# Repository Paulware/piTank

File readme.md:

<h1>Pi Tank</h1>
  This project will allow you to drive a vehicle using a laptop, optionally, you can watch 
  a a video stream on the laptop from a raspberry pi camera, mounted on the vehicle. <br>
  
<h2>Components</h2>
   <ul>
      <li>Raspberry Pi4</li>
      <li>Raspberry pi camera</li>
      <li>Raspberry motor driver pi-hat (available from <a href="https://www.adeept.com/adeept-motor-hat-for-raspberry-pi-smart-robot-car-driver_p0133.html">adeept</a>)</li>
   </ul>
   
   A lot of the testing and setup can be done without a vehicle.
   
<h1><a href="http://Paulware.github.io/piTank/docs/index.html">Step By Step Instructions (organized as test steps)</a></h1>
<hr>
<b>Note</b>  Adeept also has a similar (but different) project described: <a href="https://www.adeept.com/learn/detail-33.html">here</a>

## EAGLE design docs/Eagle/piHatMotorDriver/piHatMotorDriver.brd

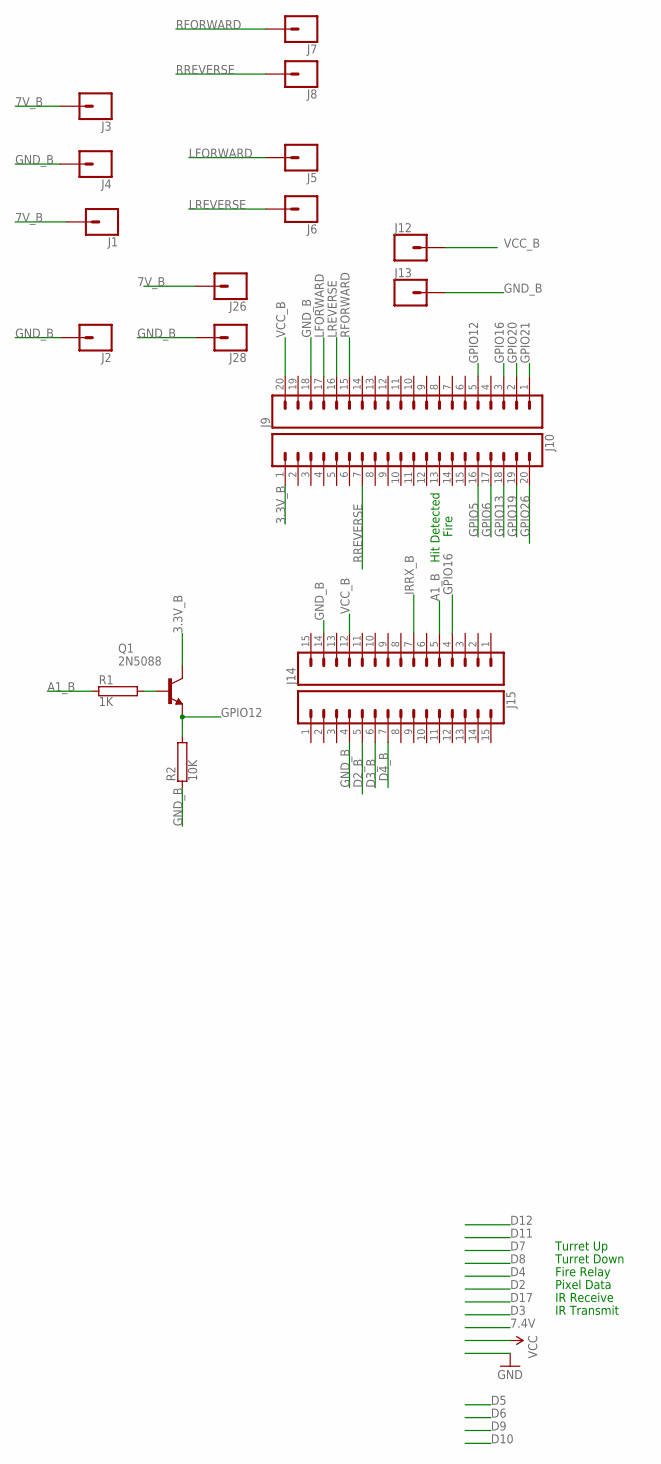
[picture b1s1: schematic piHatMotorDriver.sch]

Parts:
J1, J2, J3, J4, J5, J6, J7, J8, J12, J13, J26, J28: CONN_01; 1X01
J9, J10: CONN_20; 1X20
J14, J15: CONN_15; 1X15
Q1: 2N5088; TO92
R1: 1K; CA0001
R2: 10K; CA0001

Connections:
3.3V_B: J10.1, Q1.1 (C)
7V_B: J1.1, J3.1, J26.1; also elsewhere on the board
A1_B: J14.5, R1.1
D2_B: J15.5
D3_B: J15.6
D4_B: J15.7
GND_B: J2.1, J4.1, J9.18, J13.1, J14.14, J15.4, J28.1, R2.1; also elsewhere on the board
GPIO5: J10.16
GPIO6: J10.17
GPIO12: J9.5, Q1.3 (E), R2.2
GPIO13: J10.18
GPIO16: J9.3, J14.4
GPIO19: J10.19
GPIO20: J9.2; also elsewhere on the board
GPIO21: J9.1; also elsewhere on the board
GPIO26: J10.20
IRRX_B: J14.7
LFORWARD: J5.1, J9.17
LREVERSE: J6.1, J9.16
unnamed: Q1.2 (B), R1.2
RFORWARD: J7.1, J9.15
RREVERSE: J8.1, J10.7
VCC_B: J9.20, J12.1, J14.12

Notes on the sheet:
Turret Up
Turret Down
Fire Relay
Pixel Data
IR Receive
IR Transmit
Hit Detected
Fire

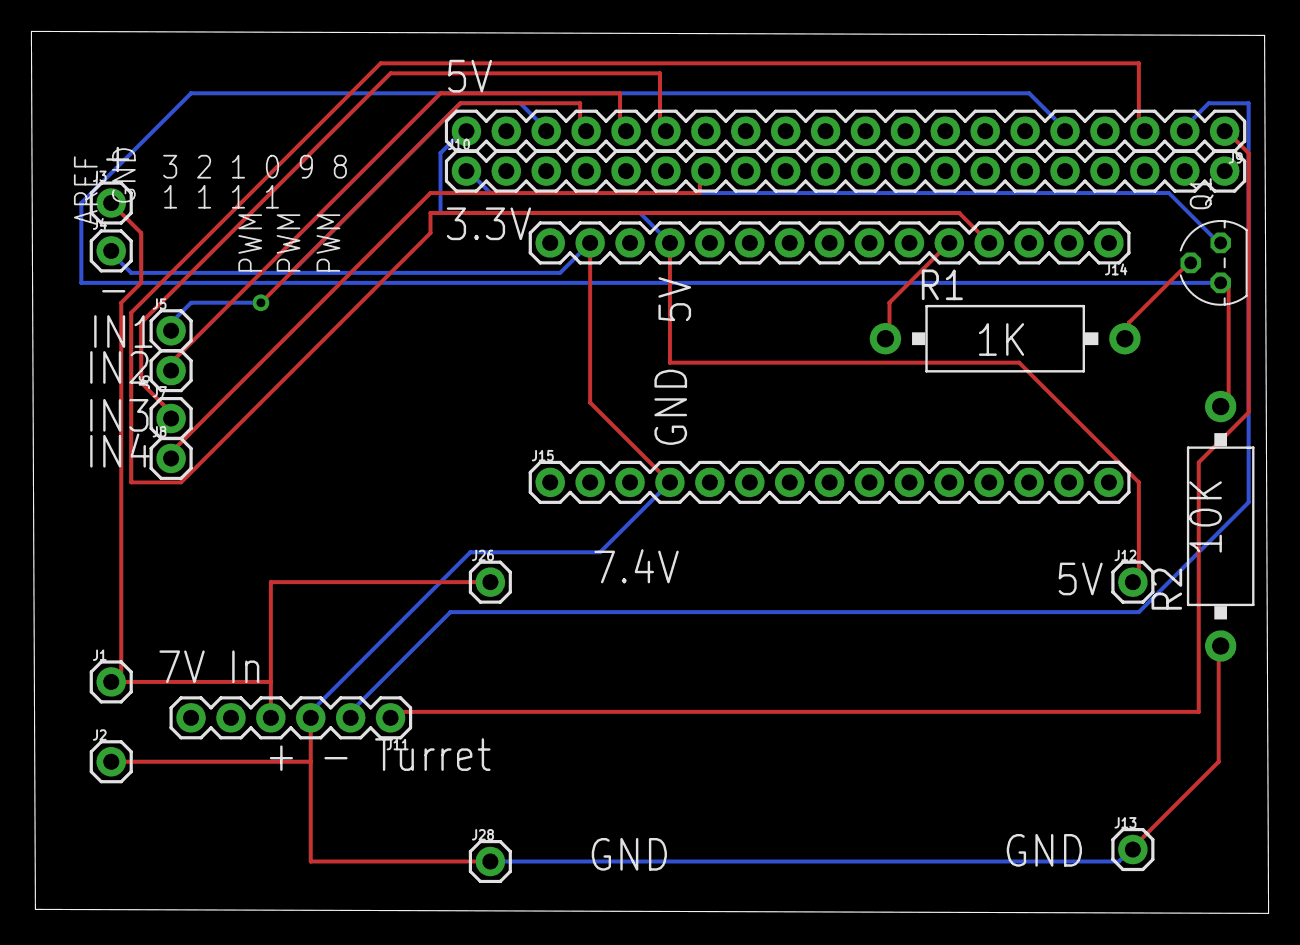
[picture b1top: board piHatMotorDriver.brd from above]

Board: 2 copper layers, 78.7 x 56.1 mm, 20 parts (0 on the bottom side), 14 nets.

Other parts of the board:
J11: 1X06

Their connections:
7V_B: J11.4; also elsewhere on the board
GND_B: J11.3; also elsewhere on the board
GPIO20: J11.2; also elsewhere on the board
GPIO21: J11.1; also elsewhere on the board

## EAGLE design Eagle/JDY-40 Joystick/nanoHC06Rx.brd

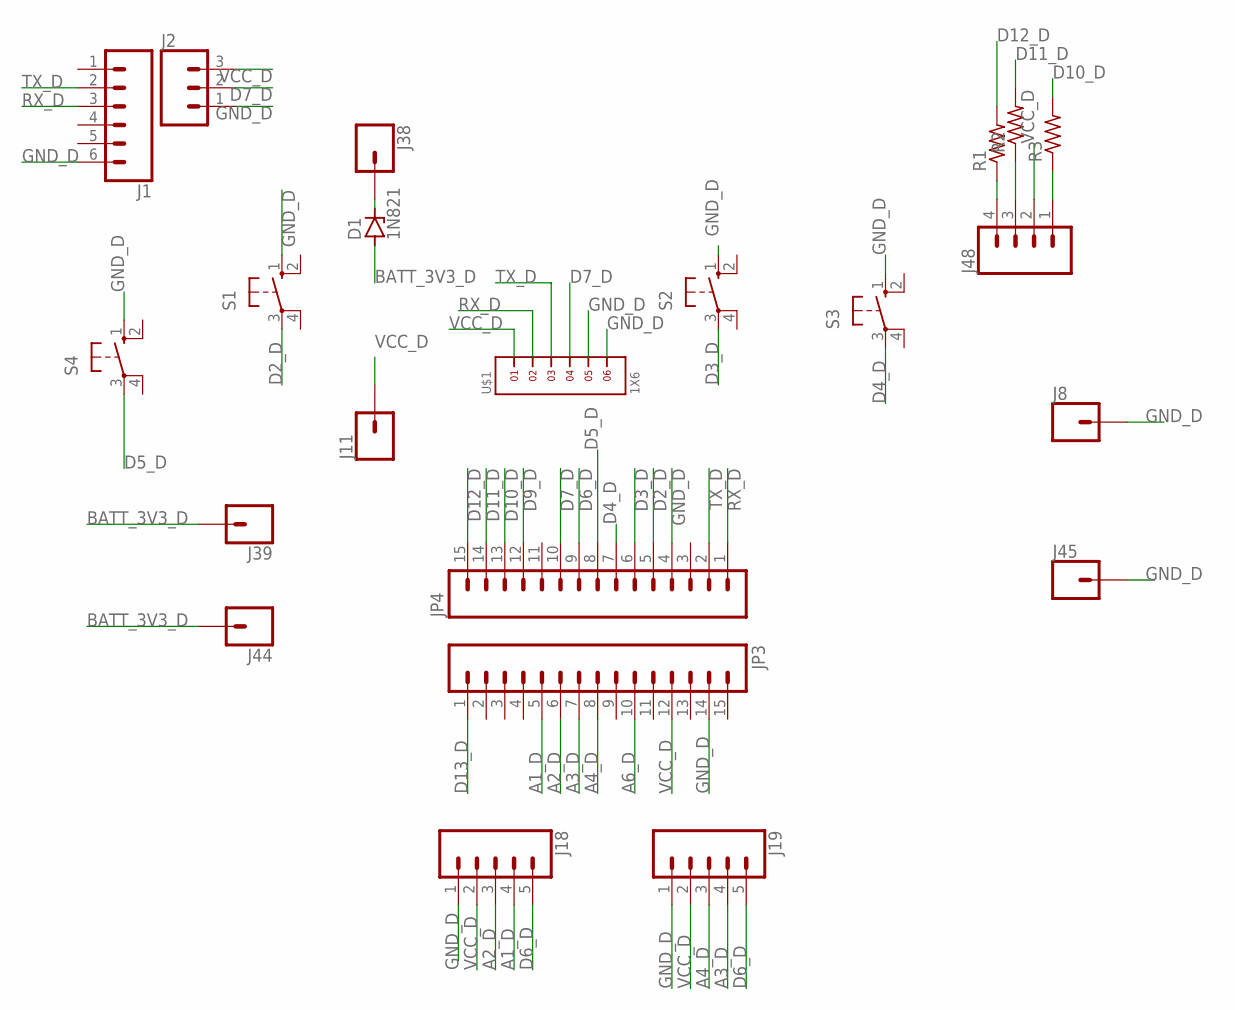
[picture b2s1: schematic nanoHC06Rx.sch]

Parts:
D1: 1N821; DO35Z10
J1: CONN_06SILK_FEMALE_PTH; 1X06
J2: CONN_03; 1X03
J8, J11, J38, J39: CONN_01; 1X01
J18, J19: CONN_05; 1X05
J44, J45: CONN_01PTH_2MM; 1X01_2MM
J48: CONN_04; 1X04
JP3, JP4: M15; 1X15@1
R1, R2, R3: R-US_0309/10; 0309/10
S1, S2, S3, S4: 40-XX; B3F-40XX
U$1: 1X6

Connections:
A1_D: J18.4, JP3.5
A2_D: J18.3, JP3.6
A3_D: J19.4, JP3.7
A4_D: J19.3, JP3.8
A6_D: JP3.10
BATT_3V3_D: D1.A, J39.1, J44.1
D2_D: JP4.5, S1.3
D3_D: JP4.6, S2.3
D4_D: JP4.7, S3.3
D5_D: JP4.8, S4.3
D6_D: J18.5, J19.5, JP4.9
D7_D: J2.2, JP4.10, U$1.4
D9_D: JP4.12
D10_D: JP4.13, R3.2
D11_D: JP4.14, R2.2
D12_D: JP4.15, R1.2
D13_D: JP3.1
GND_D: J1.6, J2.1, J8.1, J18.1, J19.1, J45.1, JP3.14, JP4.4, S1.1 (S), S2.1 (S), S3.1 (S), S4.1 (S), U$1.5, U$1.6
unnamed: D1.C, J38.1
unnamed: J48.4, R1.1
unnamed: J48.3, R2.1
unnamed: J48.1, R3.1
RX_D: J1.3, JP4.1, U$1.2
TX_D: J1.2, JP4.2, U$1.3
VCC_D: J2.3, J11.1, J18.2, J19.2, J48.2, JP3.12, U$1.1

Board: 2 copper layers, 22 parts (0 on the bottom side), 22 nets, no tracks yet.

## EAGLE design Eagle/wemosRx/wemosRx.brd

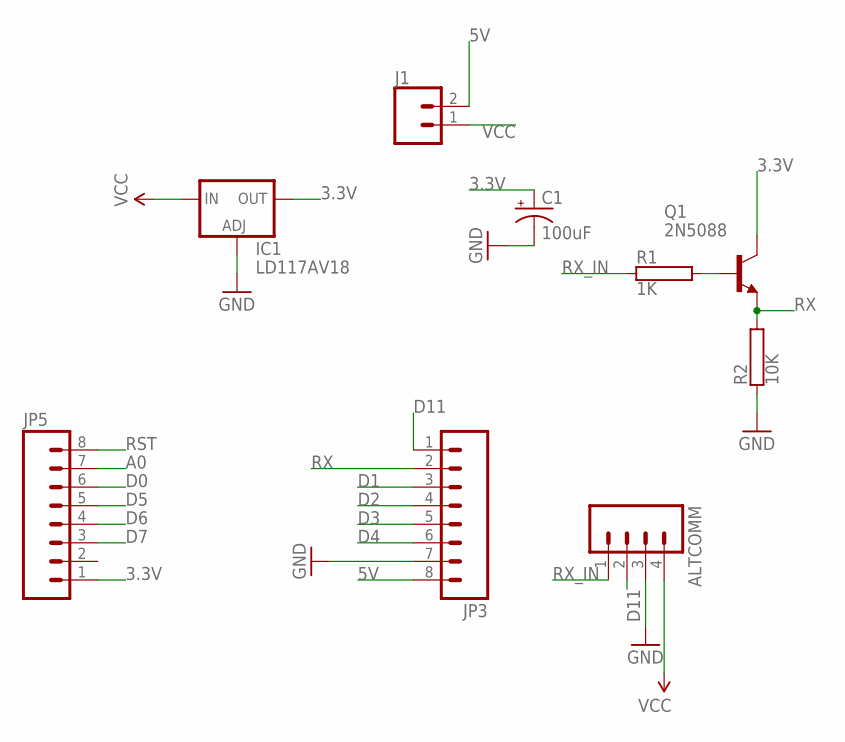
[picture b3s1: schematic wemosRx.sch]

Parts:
ALTCOMM: M04LONGPADS; 1X04_LONGPADS@1
C1: 100uF; CPOL-RADIAL-2.5MM-6.5MM
IC1: LD117AV18; TO220L1
J1: CONN_02; 1X02
JP3, JP5: M08LONGPADS; 1X08_LONGPADS
Q1: 2N5088; TO92
R1: 1K; RS1/4
R2: 10K; RS1/4

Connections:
3.3V: C1.1 (+), IC1.2 (OUT), JP5.1, Q1.1 (C)
5V: J1.2, JP3.8
A0: JP5.7
D0: JP5.6
D1: JP3.3
D2: JP3.4
D3: JP3.5
D4: JP3.6
D5: JP5.5
D6: JP5.4
D7: JP5.3
D11: ALTCOMM.2, JP3.1
GND: ALTCOMM.3, C1.2 (-), IC1.1 (ADJ), JP3.7, R2.1
unnamed: Q1.2 (B), R1.2
RST: JP5.8
RX: JP3.2, Q1.3 (E), R2.2
RX_IN: ALTCOMM.1, R1.1
VCC: ALTCOMM.4, IC1.3 (IN), J1.1

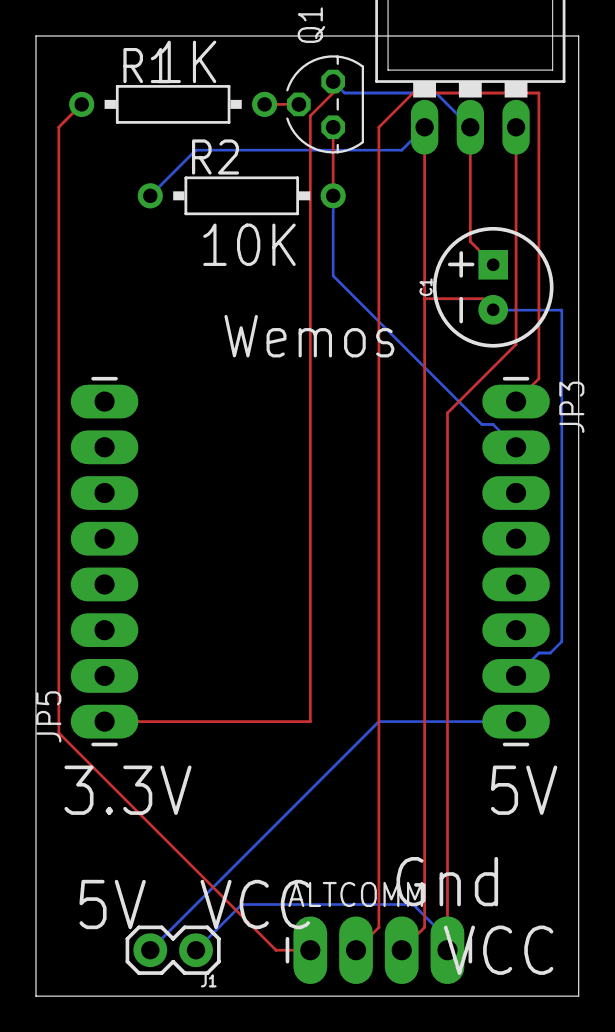
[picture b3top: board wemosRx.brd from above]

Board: 2 copper layers, 30.1 x 53.3 mm, 9 parts (0 on the bottom side), 8 nets.

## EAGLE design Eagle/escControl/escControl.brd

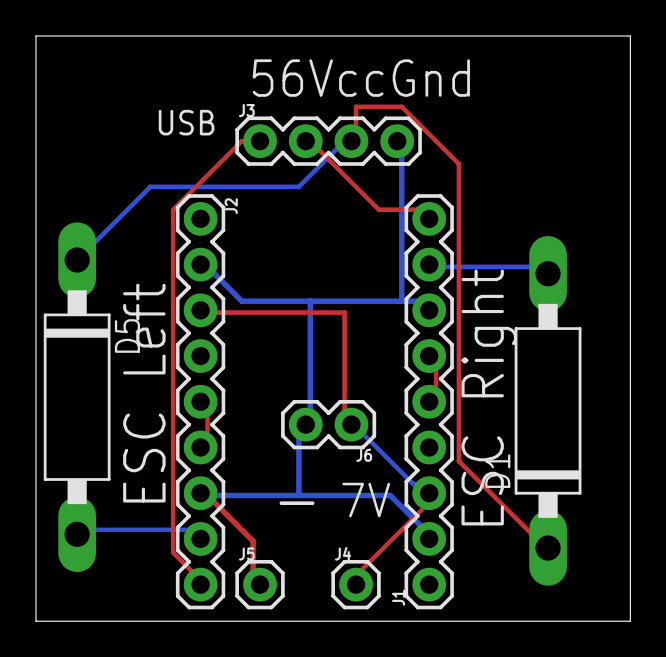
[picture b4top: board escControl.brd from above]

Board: 2 copper layers, 33.0 x 32.5 mm, 8 parts (0 on the bottom side), 9 nets.

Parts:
D1, D5: 1N5333; C1702-15
J1, J2: 1X09
J3: 1X04
J4, J5: 1X01
J6: 1X02

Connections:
7.4V: J1.3, J2.3, J4.1, J6.1
D5: J2.9, J3.1
D6: J1.9, J3.2
GND: J1.2, J1.7, J2.2, J2.7, J3.4, J5.1, J6.2
unnamed: D5.A, J2.8
unnamed: J2.5, J2.6
unnamed: D1.A, J1.8
unnamed: J1.5, J1.6
VCC: D1.C, D5.C, J3.3

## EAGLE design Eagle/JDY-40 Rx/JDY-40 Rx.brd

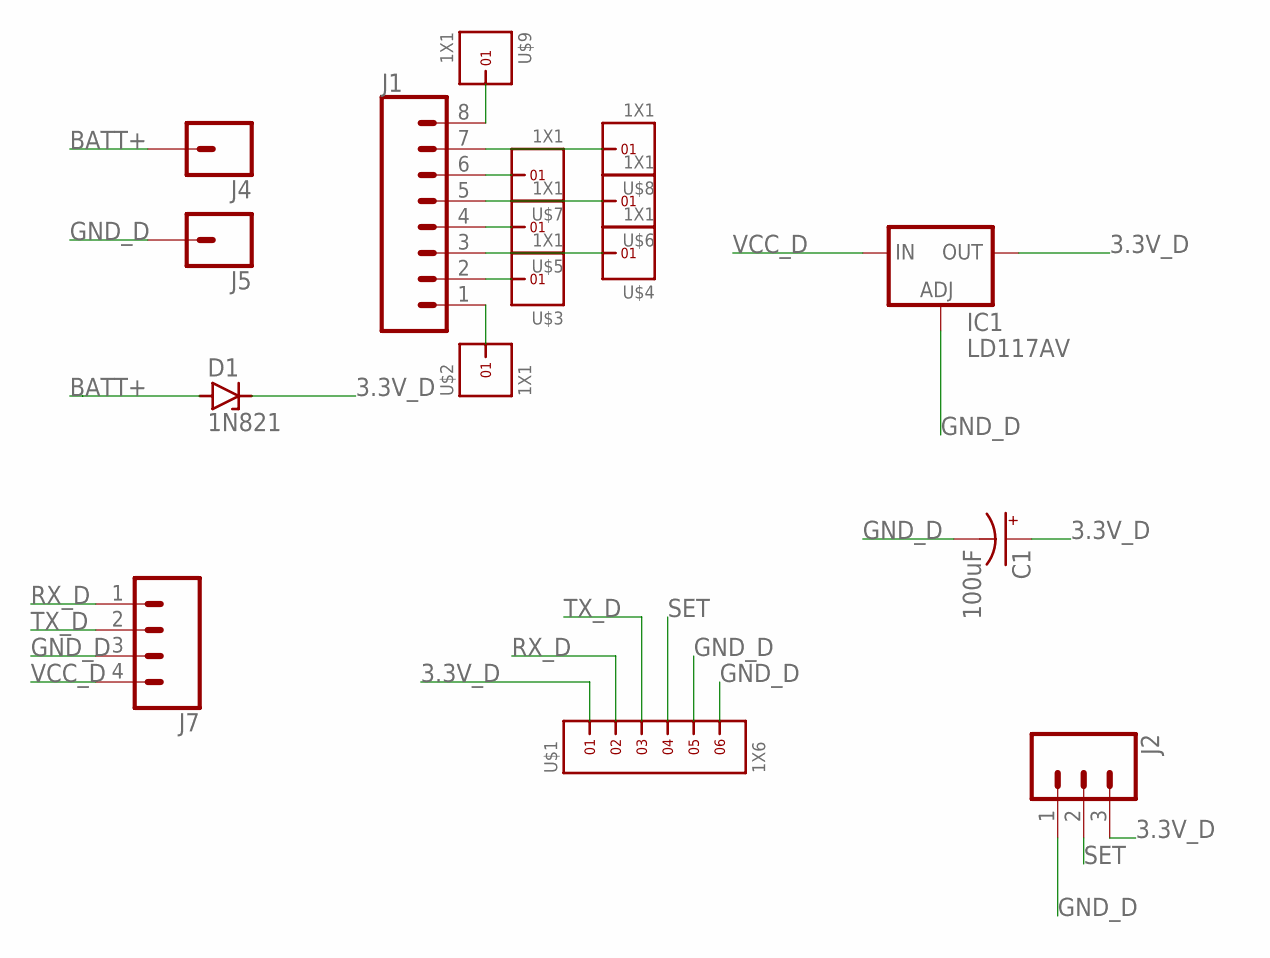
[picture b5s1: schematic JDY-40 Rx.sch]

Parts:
C1: 100uF; CPOL-RADIAL-2.5MM-6.5MM
D1: 1N821; DO35Z10
IC1: LD117AV; TO220L1
J1: CONN_08"; 1X08
J2: CONN_03; 1X03
J4, J5: CONN_01; 1X01
J7: CONN_04; 1X04
U$1: 1X6
U$2, U$3, U$4, U$5, U$6, U$7, U$8, U$9: 1X1

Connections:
3.3V_D: C1.1 (+), D1.C, IC1.2 (OUT), J2.3, U$1.1
BATT+: D1.A, J4.1
GND_D: C1.2 (-), IC1.1 (ADJ), J2.1, J5.1, J7.3, U$1.5, U$1.6
unnamed: J1.1, U$2.1
unnamed: J1.2, U$3.1
unnamed: J1.3, U$4.1
unnamed: J1.4, U$5.1
unnamed: J1.5, U$6.1
unnamed: J1.6, U$7.1
unnamed: J1.7, U$8.1
unnamed: J1.8, U$9.1
RX_D: J7.1, U$1.2
SET: J2.2, U$1.4
TX_D: J7.2, U$1.3
VCC_D: IC1.3 (IN), J7.4

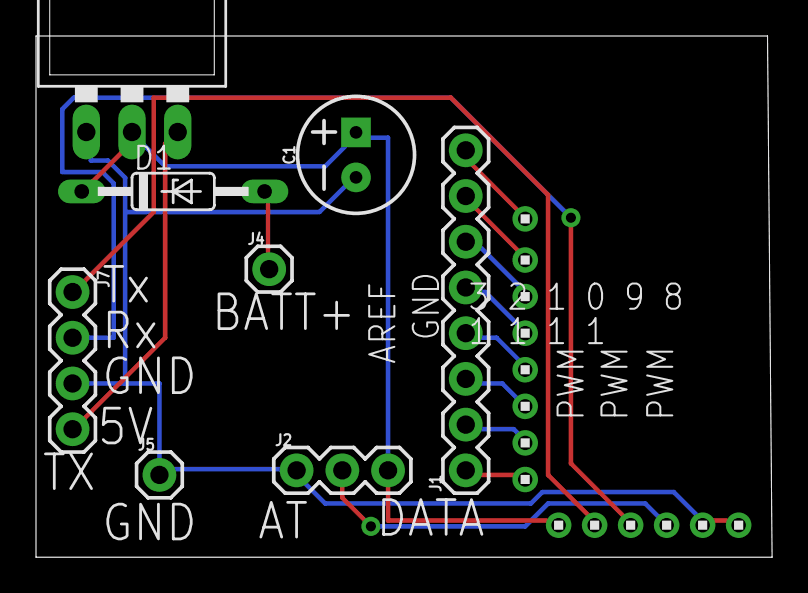
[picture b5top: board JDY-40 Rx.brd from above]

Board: 2 copper layers, 40.9 x 29.0 mm, 17 parts (0 on the bottom side), 15 nets.

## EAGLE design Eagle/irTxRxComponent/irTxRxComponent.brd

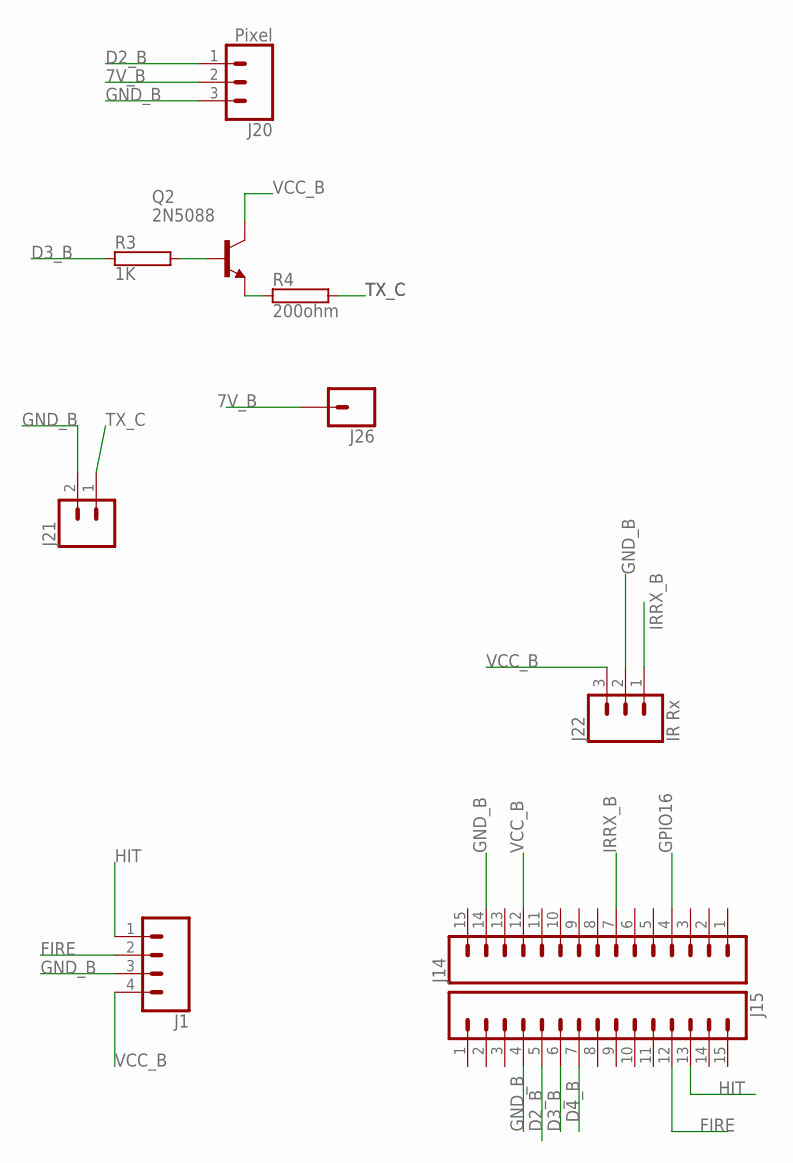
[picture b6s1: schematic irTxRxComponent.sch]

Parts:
J1: CONN_04; 1X04
J14, J15: CONN_15; 1X15
J20: Pixel; 1X03
J21: CONN_02; 1X02
J22: IR Rx; 1X03
J26: CONN_01; 1X01
Q2: 2N5088; TO92
R3: 1K; CA0001
R4: 200ohm; CA0001

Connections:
7V_B: J20.2, J26.1
D2_B: J15.5, J20.1
D3_B: J15.6, R3.1
D4_B: J15.7
FIRE: J1.2, J15.12
GND_B: J1.3, J14.14, J15.4, J20.3, J21.2, J22.2
GPIO16: J14.4
HIT: J1.1, J15.13
IRRX_B: J14.7, J22.1
unnamed: Q2.2 (B), R3.2
unnamed: Q2.3 (E), R4.1
TX_C: J21.1, R4.2
VCC_B: J1.4, J14.12, J22.3, Q2.1 (C)

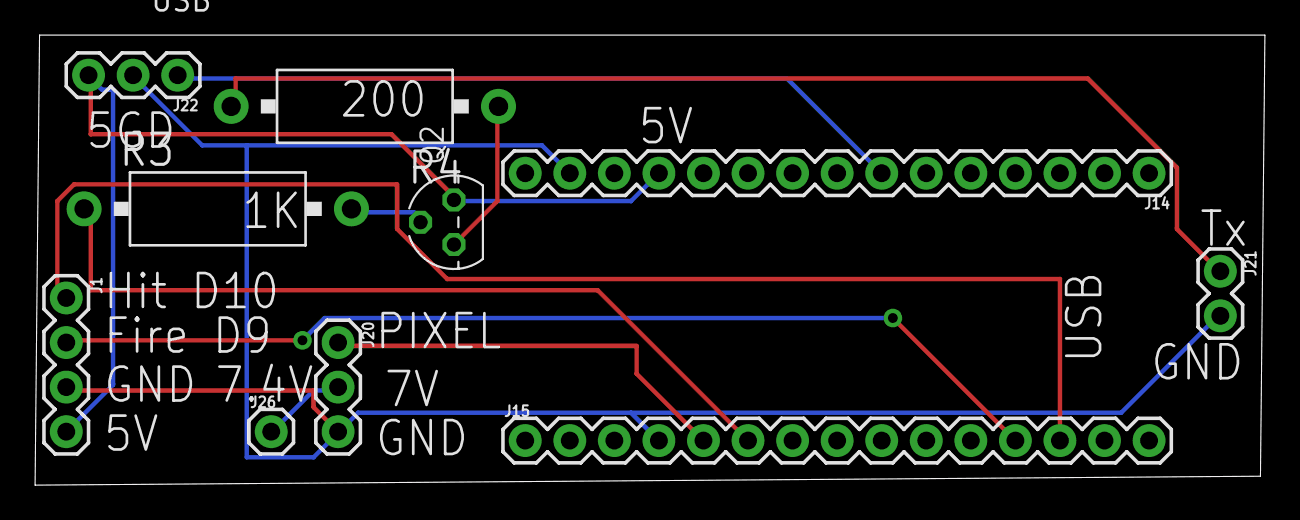
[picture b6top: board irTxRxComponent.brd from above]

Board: 2 copper layers, 70.1 x 25.7 mm, 10 parts (0 on the bottom side), 11 nets.

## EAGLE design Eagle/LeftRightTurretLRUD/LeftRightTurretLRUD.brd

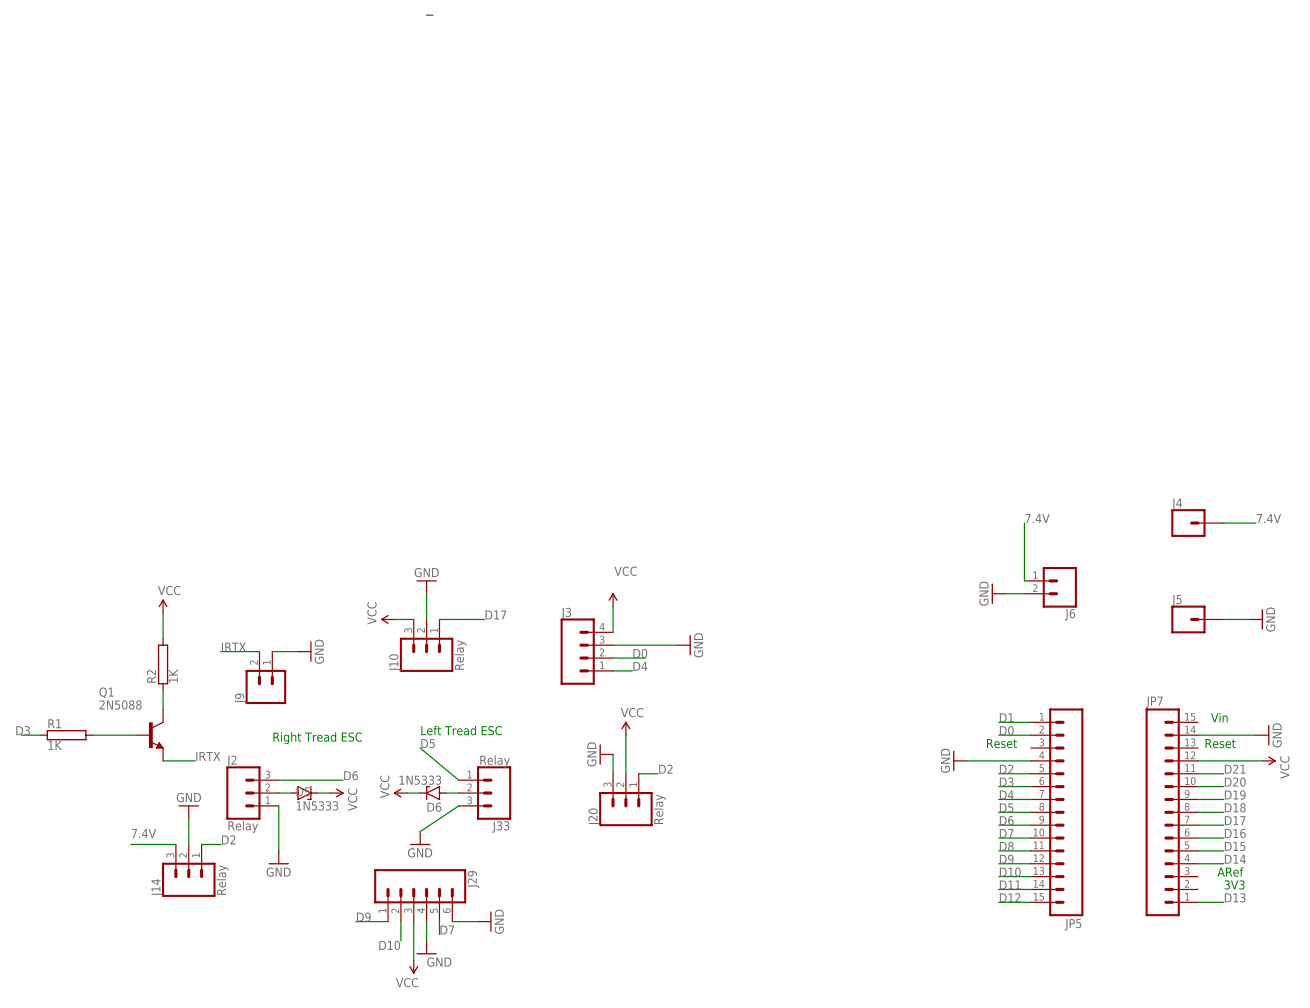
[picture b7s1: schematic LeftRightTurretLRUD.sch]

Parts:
D5, D6: 1N5333; C1702-15
J2, J10, J14, J20, J33: Relay; 1X03
J3: CONN_04; 1X04
J4, J5: CONN_01; 1X01
J6, J9: CONN_02; 1X02
J29: CONN_06NO_SILK_FEMALE_PTH; 1X06_NO_SILK
JP5, JP7: M15; 1X15@1
Q1: 2N5088; TO92
R1, R2: 1K; CA0001

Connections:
7.4V: J4.1, J6.1, J14.3
D0: J3.2, JP5.2
D1: JP5.1
D2: J14.1, J20.1, JP5.5
D3: JP5.6, R1.1
D4: J3.1, JP5.7
D5: J33.1, JP5.8
D6: J2.3, JP5.9
D7: J29.5, JP5.10
D8: JP5.11
D9: J29.1, JP5.12
D10: J29.2, JP5.13
D11: JP5.14
D12: JP5.15
D13: JP7.1
D14: JP7.4
D15: JP7.5
D16: JP7.6
D17: J10.1, JP7.7
D18: JP7.8
D19: JP7.9
D20: JP7.10
D21: JP7.11
GND: J2.1, J3.3, J5.1, J6.2, J9.1, J10.2, J14.2, J20.3, J29.4, J29.6, J33.3, JP5.4, JP7.14
IRTX: J9.2, Q1.3 (E)
unnamed: Q1.2 (B), R1.2
unnamed: Q1.1 (C), R2.1
unnamed: D5.A, J2.2
unnamed: D6.A, J33.2
VCC: D5.C, D6.C, J3.4, J10.3, J20.2, J29.3, JP7.12, R2.2

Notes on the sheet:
Reset
Vin
ARef
3V3
Left Tread ESC
Right Tread ESC

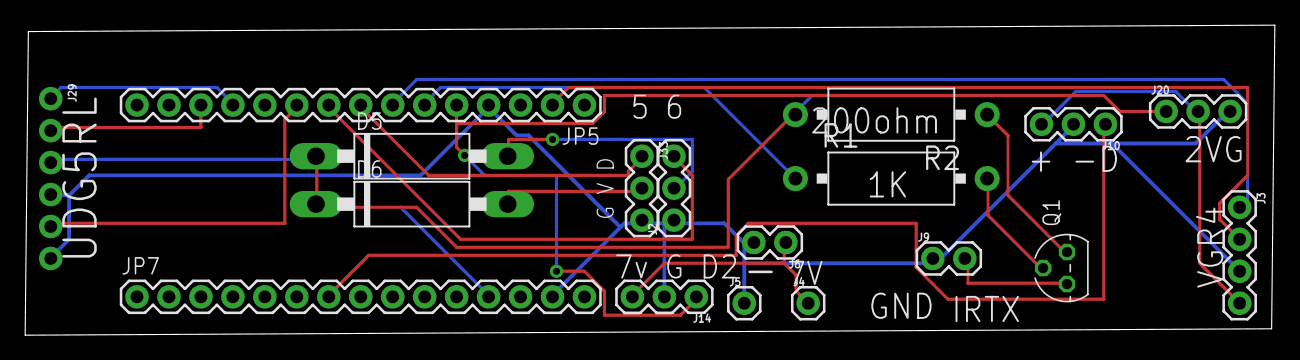
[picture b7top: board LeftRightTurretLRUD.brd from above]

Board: 2 copper layers, 99.3 x 24.6 mm, 18 parts (0 on the bottom side), 18 nets.

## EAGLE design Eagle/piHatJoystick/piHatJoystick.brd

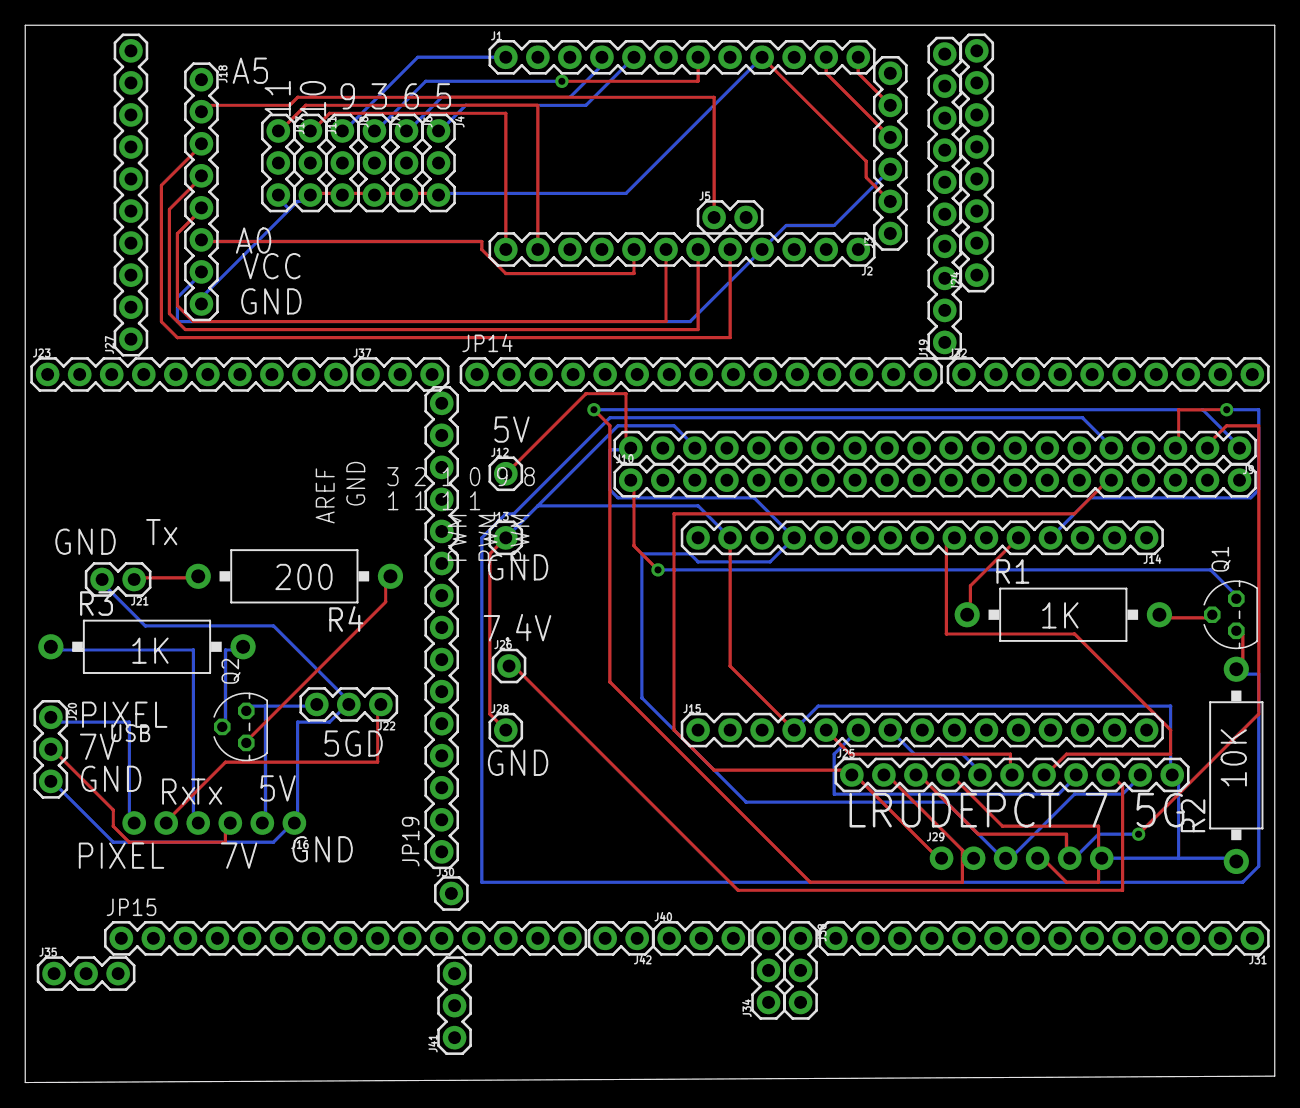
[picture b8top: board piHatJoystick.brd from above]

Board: 2 copper layers, 99.1 x 83.8 mm, 48 parts (0 on the bottom side), 39 nets.

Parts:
J1, J2: 1X12
J3: 1X06
J4, J6, J7, J8, J11, J17, J20: Pixel; 1X03
J5, J21, J42: 1X02
J9, J10: 1X20
J12, J13, J26, J28, J30: 1X01
J14, J15: 1X15
J16, J29: 1X06_NO_SILK
J18, J24: 1X08
J19, J23, J27, J32: 1X10
J22: IR Rx; 1X03
J25: 1X11
J31: 1X14
J34, J35, J37, J38, J40, J41: 1X03
JP14, JP15, JP19: 1X15@1
Q1, Q2: 2N5088; TO92
R1, R3: 1K; CA0001
R2: 10K; CA0001
R4: 200ohm; CA0001

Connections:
3.3V_B: J10.1, Q1.1
5V_C: J16.2, J22.3, Q2.1
7.4V_C: J16.3, J20.2
7V_B: J25.9, J26.1
A0_E: J2.8, J18.6
A1_B: J14.5, R1.1
A1_E: J2.7, J18.5
A2_E: J2.6, J18.4
A3_E: J2.5, J18.3
A4_E: J5.1, J18.2
D0_E: J1.11, J3.4
D1_E: J1.12, J3.5
D2_B: J15.5, J25.6
D3_B: J15.6, J25.8
D3_E: J1.7, J7.1
D4_B: J15.7, J25.5
D5_E: J1.5, J4.1
D6_E: J1.4, J6.1
D9_E: J1.1, J8.1
D10_E: J2.12, J11.1
D11_E: J2.11, J17.1
GND_B: J9.18, J13.1, J14.14, J15.4, J25.4, J25.11, J28.1, J29.4, J29.6, R2.1
GND_C: J16.1, J20.3, J21.2, J22.2
GND_E: J1.9, J3.2, J4.3, J6.3, J7.3, J8.3, J11.3, J17.3, J18.8
GPIO5: J10.16, J25.1, J29.1
GPIO12: J9.5, Q1.3, R2.2
GPIO16: J9.3, J14.4
GPIO20: J9.2, J25.3, J29.5
GPIO21: J9.1, J25.2, J29.2
IRRX_B: J14.7, J25.7
unnamed: Q1.2, R1.2
unnamed: Q2.2, R3.2
unnamed: Q2.3, R4.1
PIXEL_C: J16.6, J20.1
RXIR_C: J16.5, J22.1
TXIR_C: J16.4, R3.1
TX_C: J21.1, R4.2
VCC_B: J9.20, J12.1, J14.12, J25.10, J29.3
VCC_E: J2.4, J3.3, J18.7

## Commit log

2020-04-11 setup
2020-04-11 dtoverlay
2020-04-13 setup webcam
2020-04-16 setup mjpg-streamer
2020-04-16 mjpg-streamer
2020-04-16 REadme
2020-04-16 arduino
2020-04-16 tutorial
2020-04-16 docs
2020-04-16 repo
2020-04-16 eagle
2020-04-17 ESC speed controller
2020-04-17 Enable camera
2020-04-18 Binary numbers
2020-04-20 heng long
2020-04-20 streamer
2020-04-21 Remove variant images
2020-04-21 unknown
2020-04-21 communication
2020-04-21 comm
2020-04-22 connect.sh
2020-04-22 Add tank Control
2020-04-22 remove runTank.sh
2020-04-23 all.sh
2020-04-23 design
2020-04-23 photo
2020-04-29 Bind HC05 and HC06
2020-04-29 Added tera-term
2020-04-29 TeraTerm
2020-04-29 ter term
2020-05-01 esp32 bluetooth
2020-05-07 ESC control from bluetooth
2020-05-12 Requirements
2020-05-20 joystick
2020-05-21 jdy40
2020-05-22 docs'
2020-05-23 irTxRx
2020-05-23 ircomponent
2020-05-29 Added Chrome App
2020-06-01 Broadcast to 10.3.141.255
2020-06-01 setBroadcast
2020-06-01 task
2020-06-01 eagle pcb-40 rx
2020-06-02 websocket
2020-06-03 hello
2020-06-03 Websocket design
2020-06-04 esp32cam
2020-06-05 arduino yo
2020-06-05 binary remove
2020-06-16 forward
2020-06-17 websocketserver
2020-06-17 port forward
2020-06-23 ddns.net
2020-06-23 yete
2020-06-23 8080
2020-06-23 ip address
2020-06-26 webserver
2020-07-26 Proof of concept
2020-07-29 click
2020-08-04 modify pictures
2020-08-27 Lesson 1
2020-09-21 ssid
2020-11-15 wasd
2020-11-15 login
2020-11-15 value
2020-11-16 external port
2020-11-16 king tiger
2020-11-18 added hit to webserver
2020-11-18 hitcounts
2021-08-29 steps
2021-08-30 Schematic

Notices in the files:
parts and their libraries:
SparkFun-Connectors: Licensing: Creative Commons ShareAlike 4.0 International - https://creativecommons.org/licenses/by-sa/4.0
